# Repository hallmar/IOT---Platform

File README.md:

# Modular IOT Platform
Commissioned a modular IOT Platform for teaching purposes. There's a basic program in the 'Software' folder which is simply an IO test for the buttons and a test for the OLED.

Mouser Cart: https://www.mouser.com/ProjectManager/ProjectDetail.aspx?AccessID=9a8a02e45e

## Designed With

* Eagle CAD
* Arduino IDE

## Versioning
* 1.0 - [Hardware] Original hardware made
* 1.0 - [Software] Original 'basic' software written
## Authors

* **Hallmar Gauti Halldórsson**
* **Markus Pfeil**

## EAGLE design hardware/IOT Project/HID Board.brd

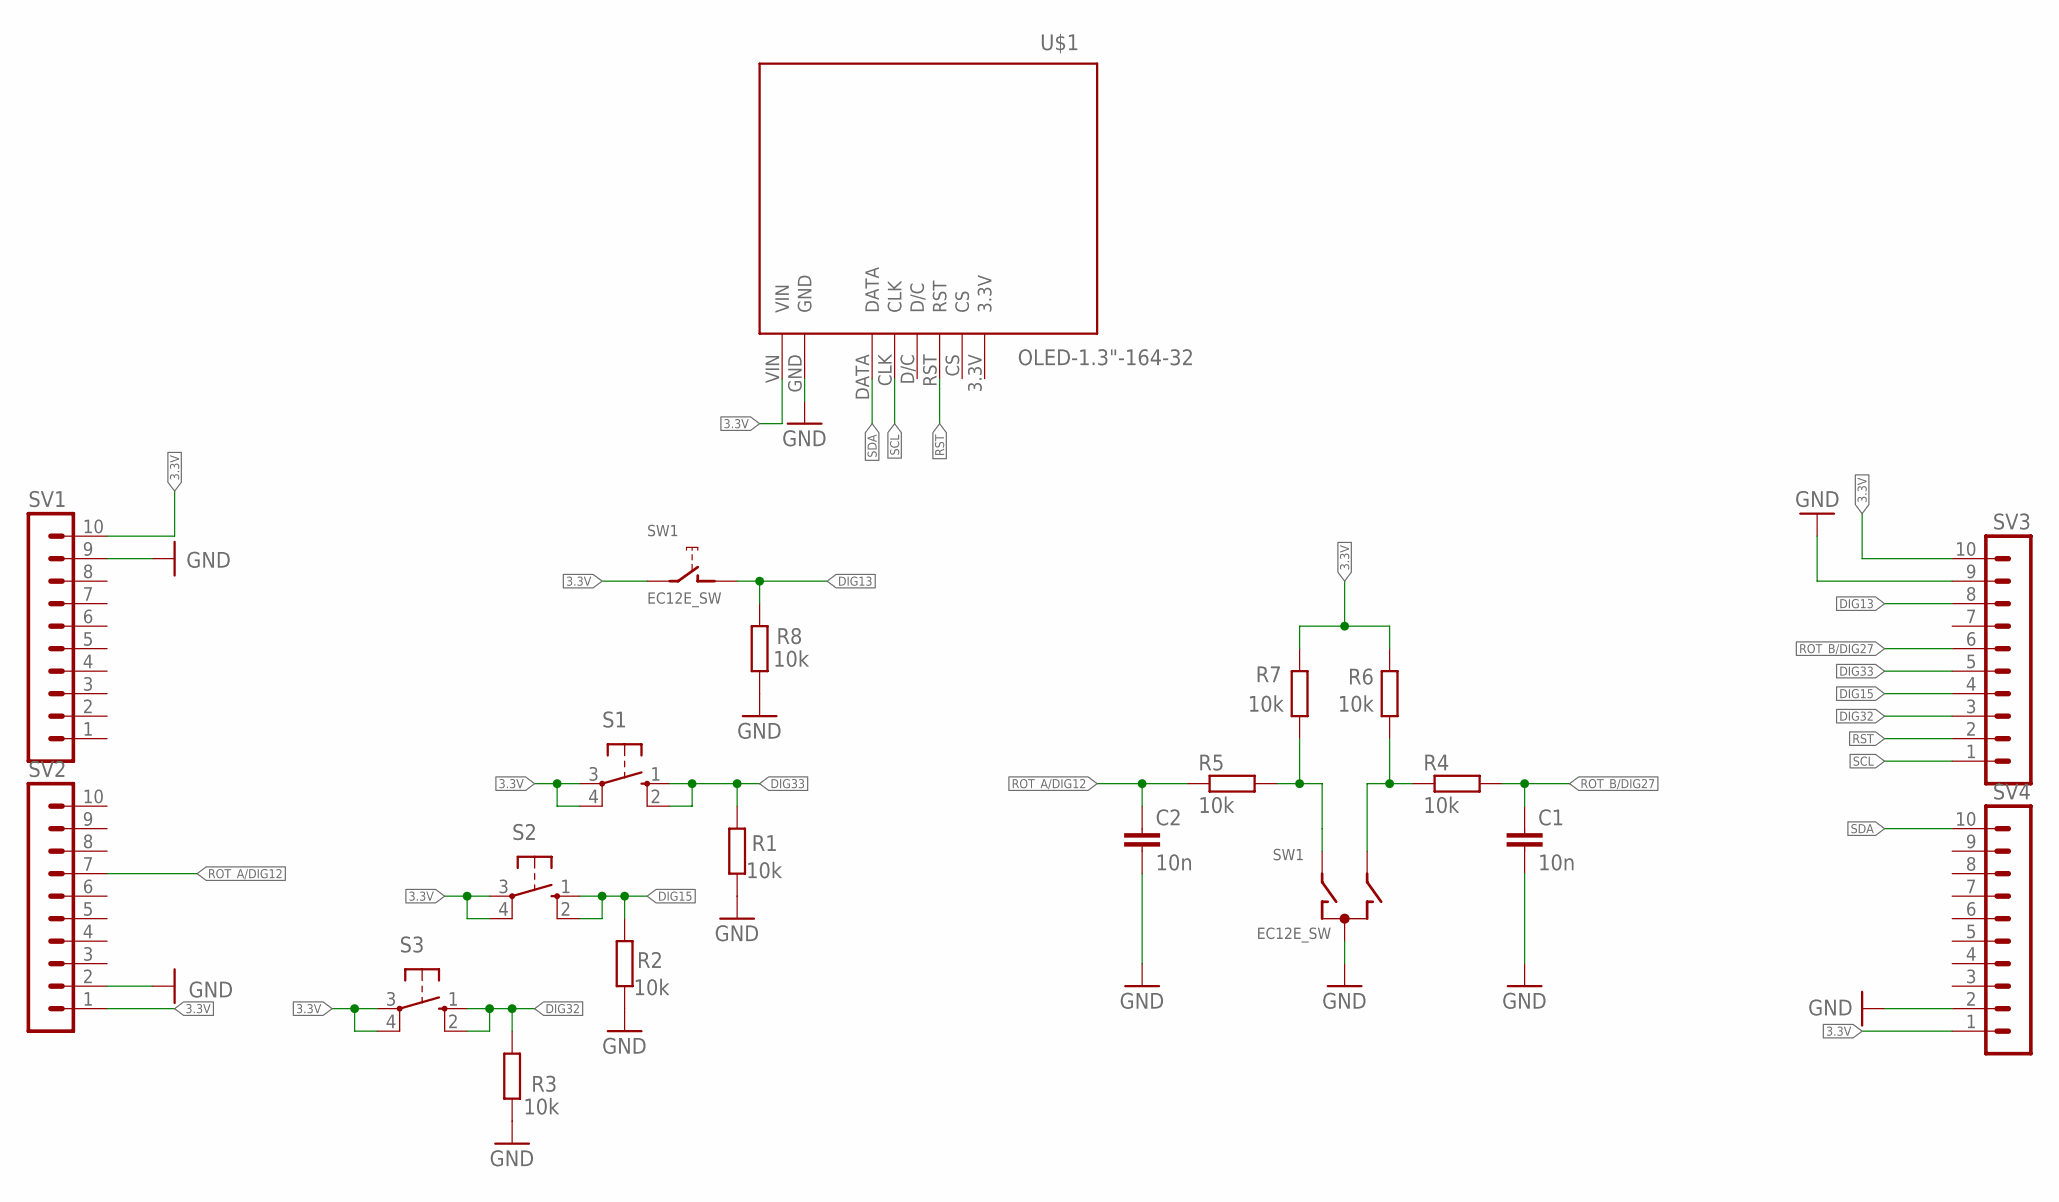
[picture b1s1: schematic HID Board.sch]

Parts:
C1, C2: 10n; C1206
R1, R2, R3, R4, R5, R6, R7, R8: 10k; M1206
S1, S2, S3: 10-XX; B3F-10XX
SV1, SV2, SV3, SV4: MA10-1
SW1: EC12E_SW; ALPS_EC12E_SW
U$1: OLED-1.3"-164-32

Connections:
3.3V: R6.2, R7.2, S1.3, S1.4 (P1), S2.3, S2.4 (P1), S3.3, S3.4 (P1), SV1.10, SV2.1, SV3.10, SV4.1, SW1.E (2), U$1.VIN
DIG13: R8.2, SV3.8, SW1.D (1)
DIG15: R2.2, S2.1 (S), S2.2 (S1), SV3.4
DIG32: R3.2, S3.1 (S), S3.2 (S1), SV3.3
DIG33: R1.2, S1.1 (S), S1.2 (S1), SV3.5
GND: C1.2, C2.2, R1.1, R2.1, R3.1, R8.1, SV1.9, SV2.2, SV3.9, SV4.2, SW1.C, U$1.GND
unnamed: R5.2, R7.1, SW1.A
unnamed: R4.1, R6.1, SW1.B
ROT_A/DIG12: C2.1, R5.1, SV2.7
ROT_B/DIG27: C1.1, R4.2, SV3.6
RST: SV3.2, U$1.RST
SCL: SV3.1, U$1.CLK
SDA: SV4.10, U$1.DATA

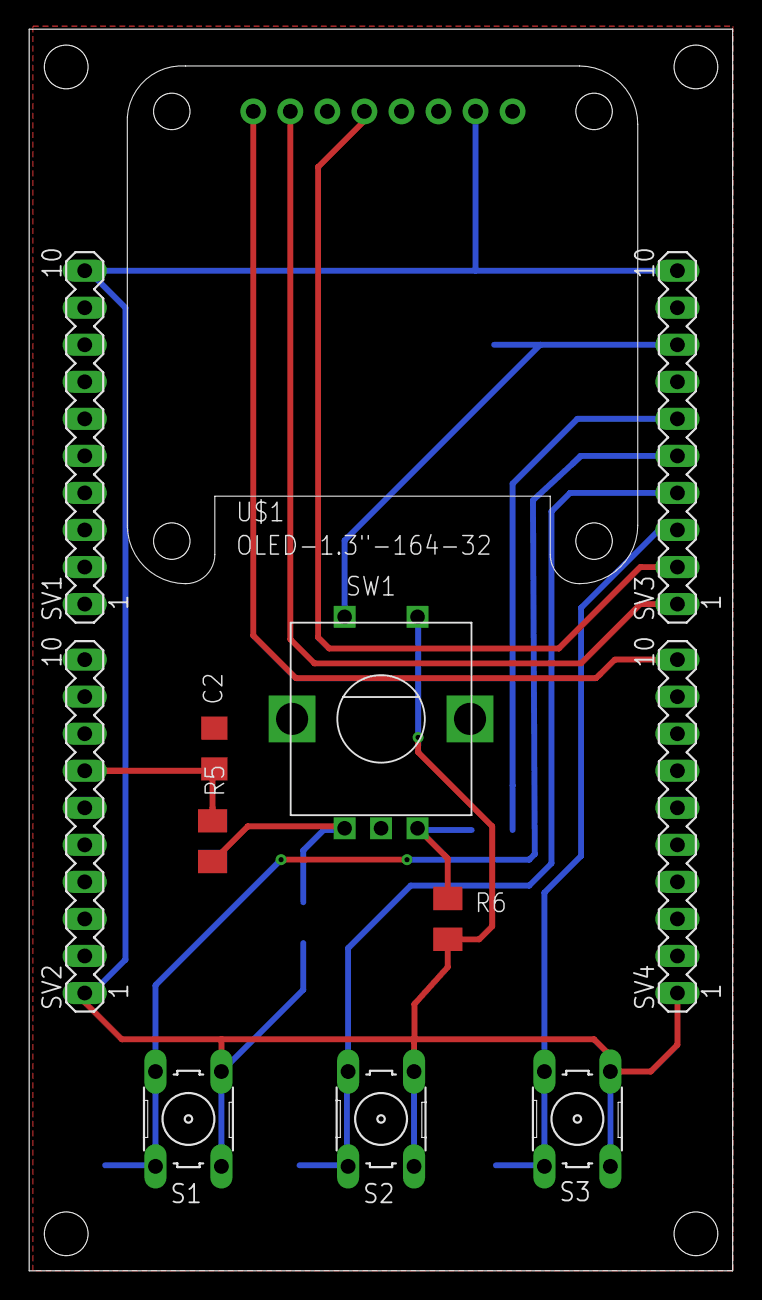
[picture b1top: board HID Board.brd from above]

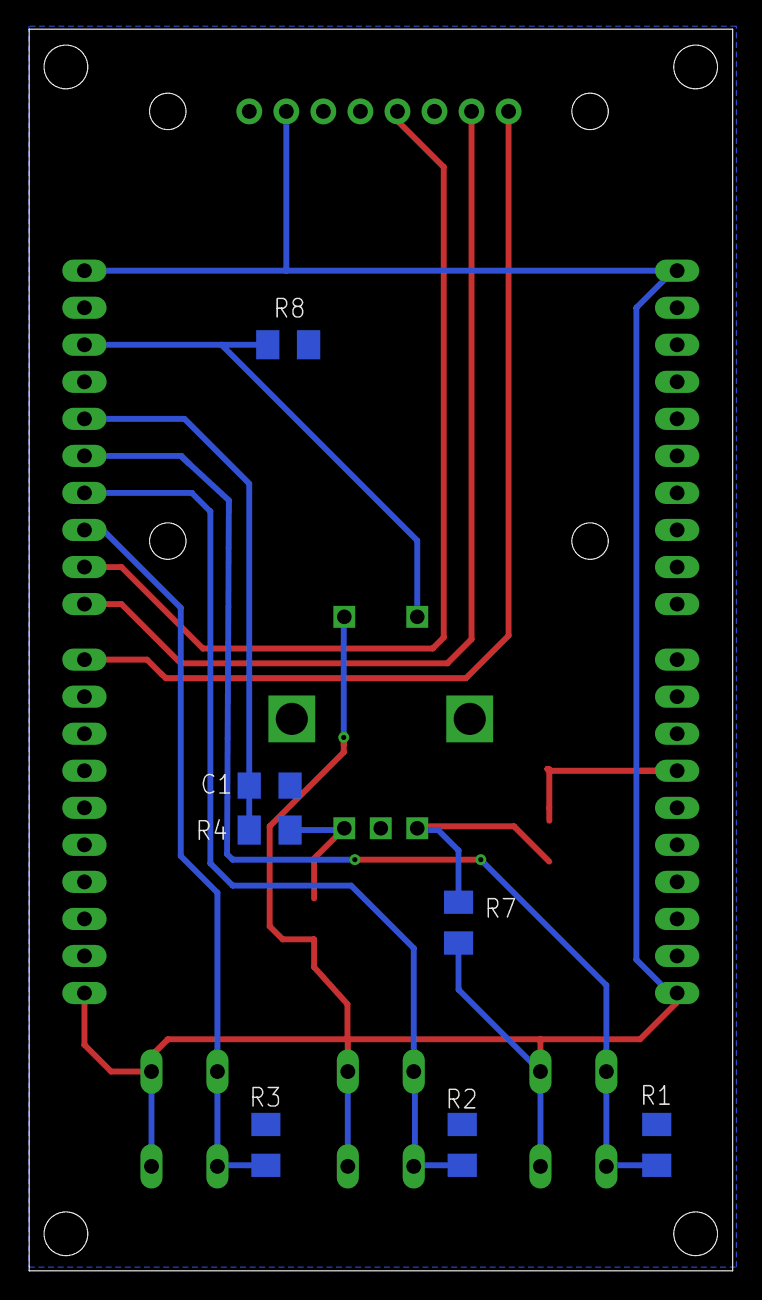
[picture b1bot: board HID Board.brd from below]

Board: 2 copper layers, 48.2 x 85.1 mm, 19 parts (7 on the bottom side), 13 nets.

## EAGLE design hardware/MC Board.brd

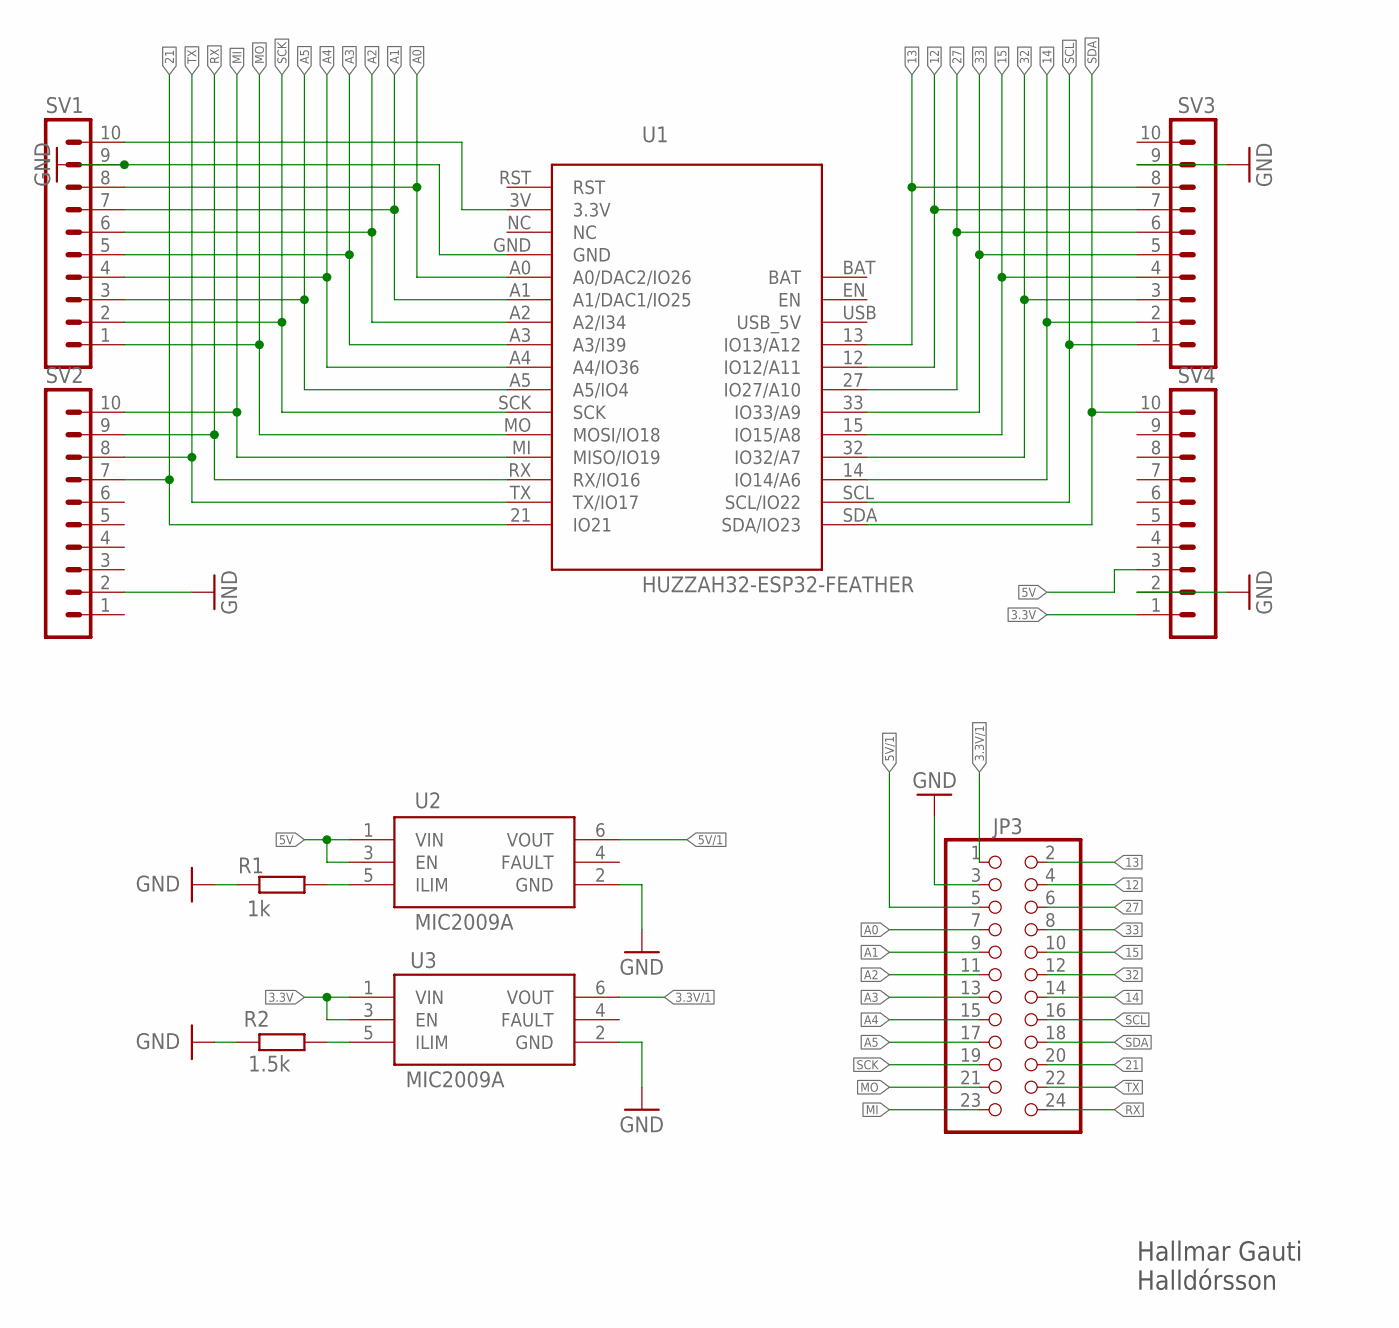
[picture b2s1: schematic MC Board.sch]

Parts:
JP3: PINHD-2X12/90; 2X12/90
R1: 1k; M1206
R2: 1.5k; M1206
SV1, SV2, SV3, SV4: MA10-1
U1: HUZZAH32-ESP32-FEATHER; ESP32-FEATHER
U2, U3: MIC2009A

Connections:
3.3V: SV4.1, U3.1 (VIN), U3.3 (EN)
3.3V/1: JP3.1, U3.6 (VOUT)
5V: SV4.3, U2.1 (VIN), U2.3 (EN)
5V/1: JP3.5, U2.6 (VOUT)
12: JP3.4, SV3.7, U1.12 (IO12/A11)
13: JP3.2, SV3.8, U1.13 (IO13/A12)
14: JP3.14, SV3.2, U1.14 (IO14/A6)
15: JP3.10, SV3.4, U1.15 (IO15/A8)
21: JP3.20, SV2.7, U1.21 (IO21)
27: JP3.6, SV3.6, U1.27 (IO27/A10)
32: JP3.12, SV3.3, U1.32 (IO32/A7)
33: JP3.8, SV3.5, U1.33 (IO33/A9)
A0: JP3.7, SV1.8, U1.A0 (A0/DAC2/IO26)
A1: JP3.9, SV1.7, U1.A1 (A1/DAC1/IO25)
A2: JP3.11, SV1.6, U1.A2 (A2/I34)
A3: JP3.13, SV1.5, U1.A3 (A3/I39)
A4: JP3.15, SV1.4, U1.A4 (A4/IO36)
A5: JP3.17, SV1.3, U1.A5 (A5/IO4)
GND: JP3.3, R1.2, R2.1, SV1.9, SV2.2, SV3.9, SV4.2, U1.GND, U2.2 (GND), U3.2 (GND)
MI: JP3.23, SV2.10, U1.MI (MISO/IO19)
MO: JP3.21, SV1.1, U1.MO (MOSI/IO18)
unnamed: SV1.10, U1.3V (3.3V)
unnamed: R2.2, U3.5 (ILIM)
unnamed: R1.1, U2.5 (ILIM)
RX: JP3.24, SV2.9, U1.RX (RX/IO16)
SCK: JP3.19, SV1.2, U1.SCK
SCL: JP3.16, SV3.1, U1.SCL (SCL/IO22)
SDA: JP3.18, SV4.10, U1.SDA (SDA/IO23)
TX: JP3.22, SV2.8, U1.TX (TX/IO17)

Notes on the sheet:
Hallmar Gauti Halldórsson

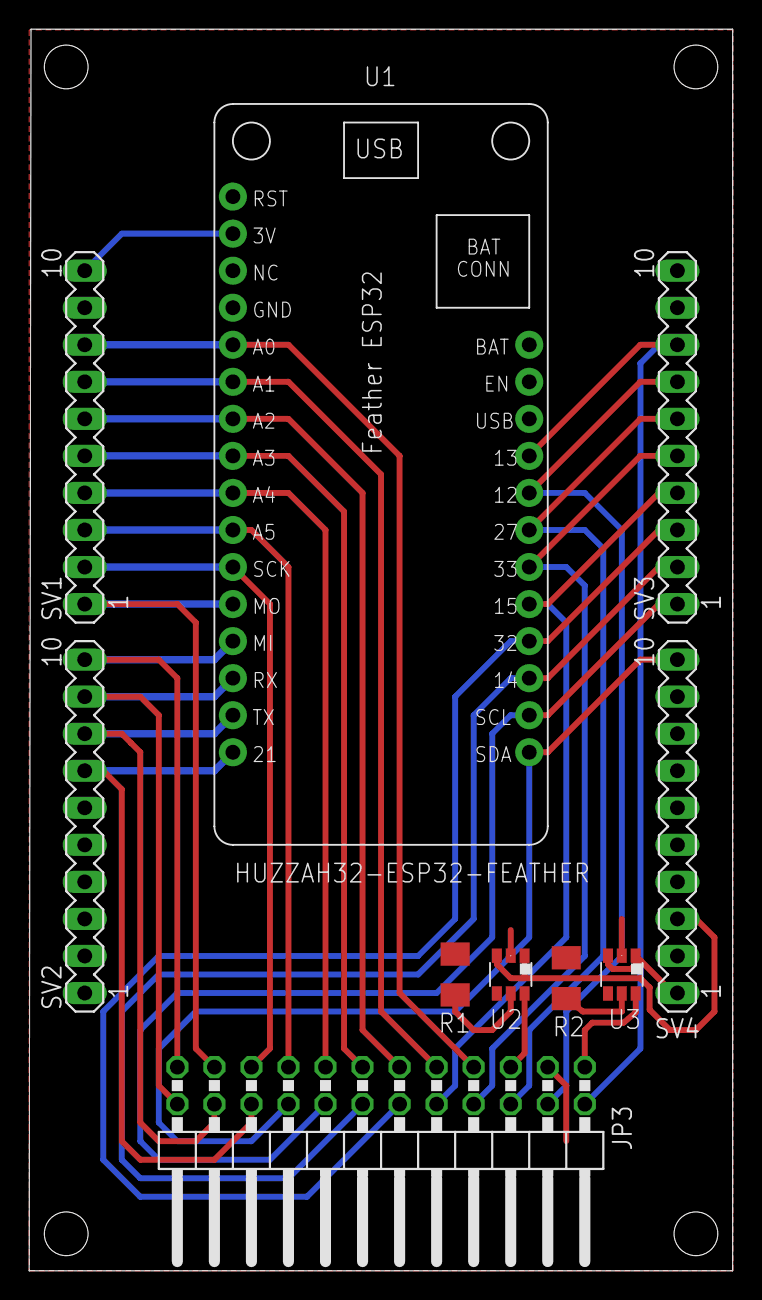
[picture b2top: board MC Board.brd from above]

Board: 2 copper layers, 48.2 x 85.1 mm, 10 parts (0 on the bottom side), 29 nets.

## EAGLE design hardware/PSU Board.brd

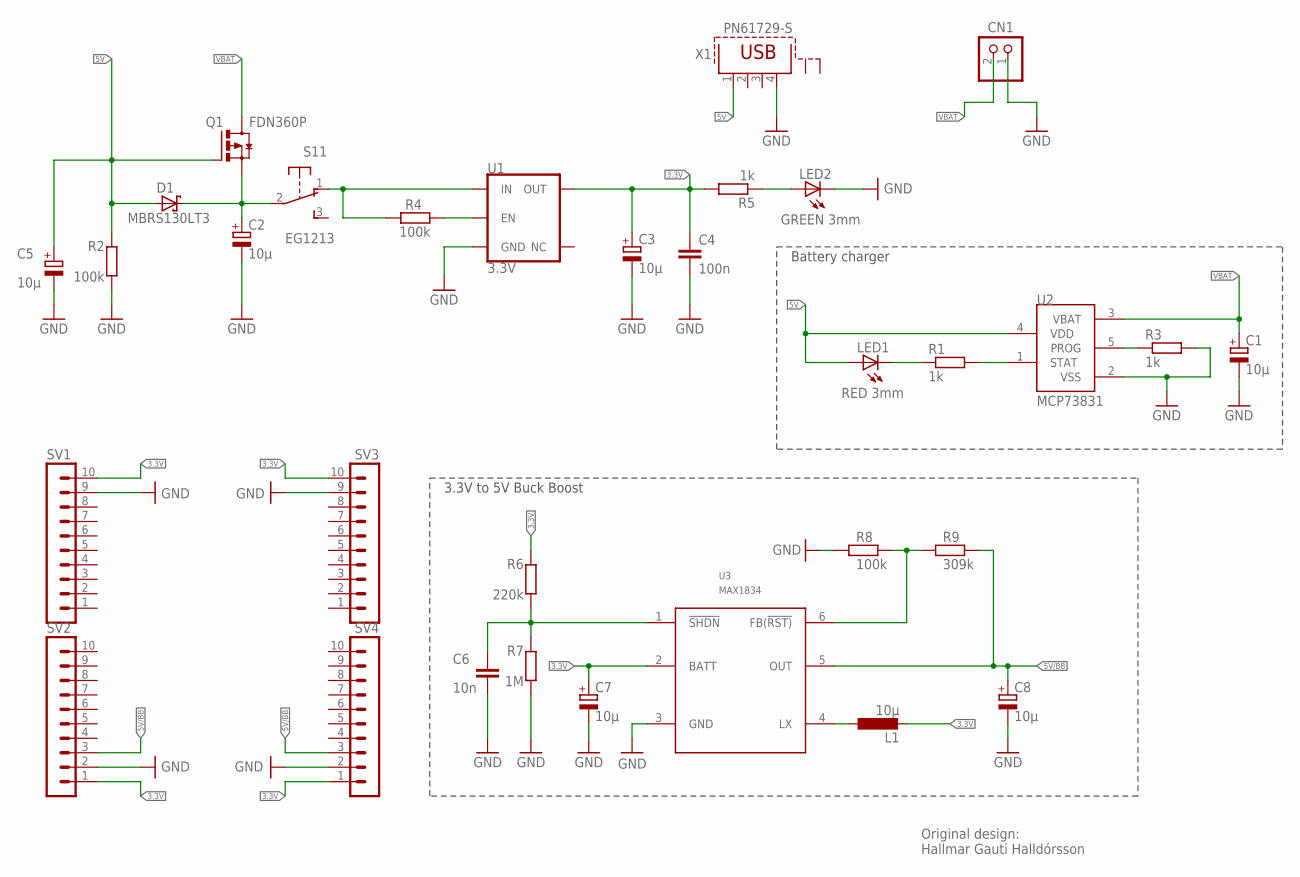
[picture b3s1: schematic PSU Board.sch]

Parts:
C1, C2, C3, C5, C7, C8: 10µ; 140CLH-0810
C4: 100n; C1206
C6: 10n; C1206
CN1: JST_2PIN-SMT; JST-PH-2-SMT
D1: MBRS130LT3; SMB
L1: 10µ; L3216C
LED1: RED 3mm; LED3MM
LED2: GREEN 3mm; LED3MM
Q1: FDN360P; SUPER-SOT3
R1, R3, R5: 1k; M1206
R2, R4, R8: 100k; M1206
R6: 220k; M1206
R7: 1M; M1206
R9: 309k; M1206
S1: EG1213
SV1, SV2, SV3, SV4: MA10-1
U1: 3.3V; SOT23-5
U2: MCP73831; SOT23-5L
U3: MAX1834; SOT23-6
X1: PN61729-S

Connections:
3.3V: C3.+, C4.1, C7.+, L1.2, R5.2, R6.2, SV1.10, SV2.1, SV3.10, SV4.1, U1.5 (OUT), U3.2 (BATT)
5V: C5.+, D1.A, LED1.A, Q1.1 (G), R2.2, U2.4 (VDD), X1.1
5V/BB: C8.+, R9.1, SV2.3, SV4.3, U3.5 (OUT)
GND: C1.-, C2.-, C3.-, C4.2, C5.-, C6.2, C7.-, C8.-, CN1.1 (2), LED2.K (C), R2.1, R3.2, R7.1, R8.2, SV1.9, SV2.2, SV3.9, SV4.2, U1.2 (GND), U2.2 (VSS), U3.3 (GND), X1.4
unnamed: C2.+, D1.C, Q1.2 (S), S1.2
unnamed: R1.2, U2.1 (STAT)
unnamed: R4.2, S1.1 (O), U1.1 (IN)
unnamed: LED1.K (C), R1.1
unnamed: R3.1, U2.5 (PROG)
unnamed: R4.1, U1.3 (EN)
unnamed: LED2.A, R5.1
unnamed: C6.1, R6.1, R7.2, U3.1 (!SHDN)
unnamed: L1.1, U3.4 (LX)
unnamed: R8.1, R9.2, U3.6 (FB(!RST))
VBAT: C1.+, CN1.2 (1), Q1.3 (D), U2.3 (VBAT)

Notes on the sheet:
Original design: Hallmar Gauti Halldórsson
Battery charger
3.3V to 5V Buck Boost

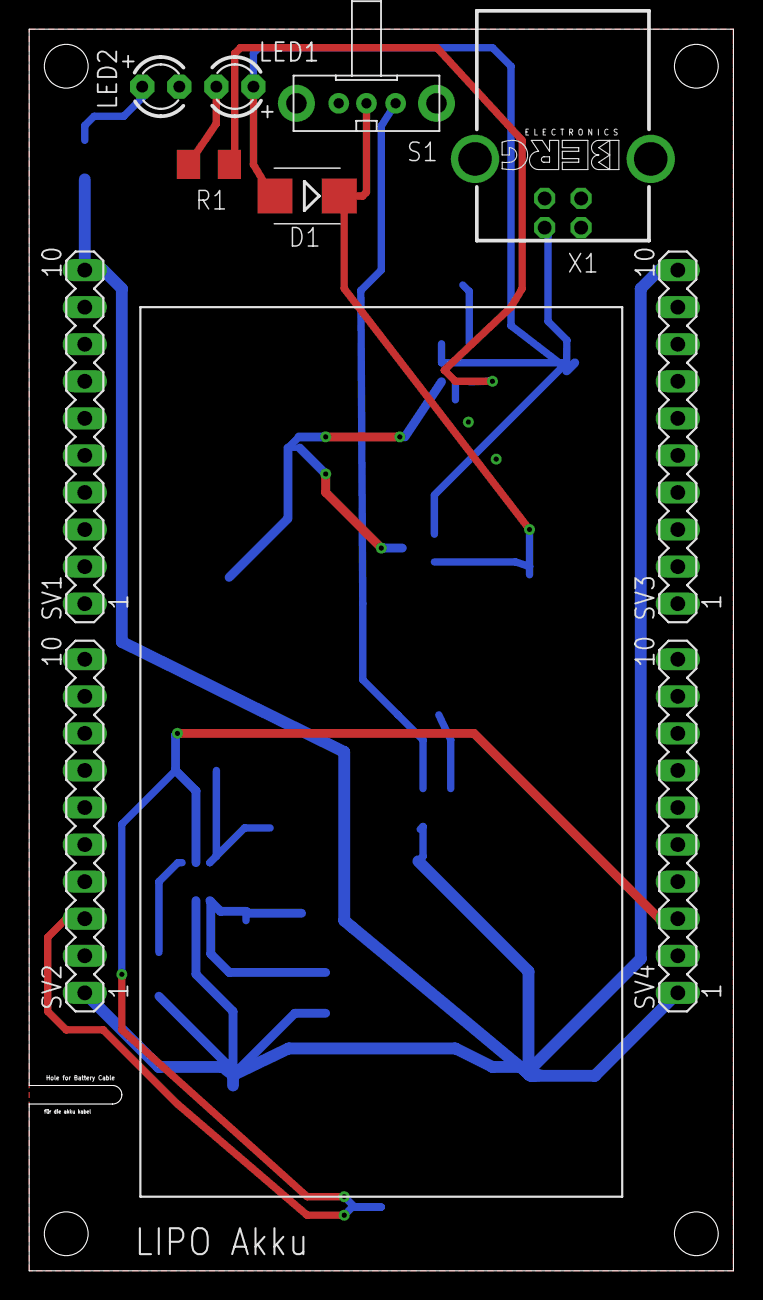
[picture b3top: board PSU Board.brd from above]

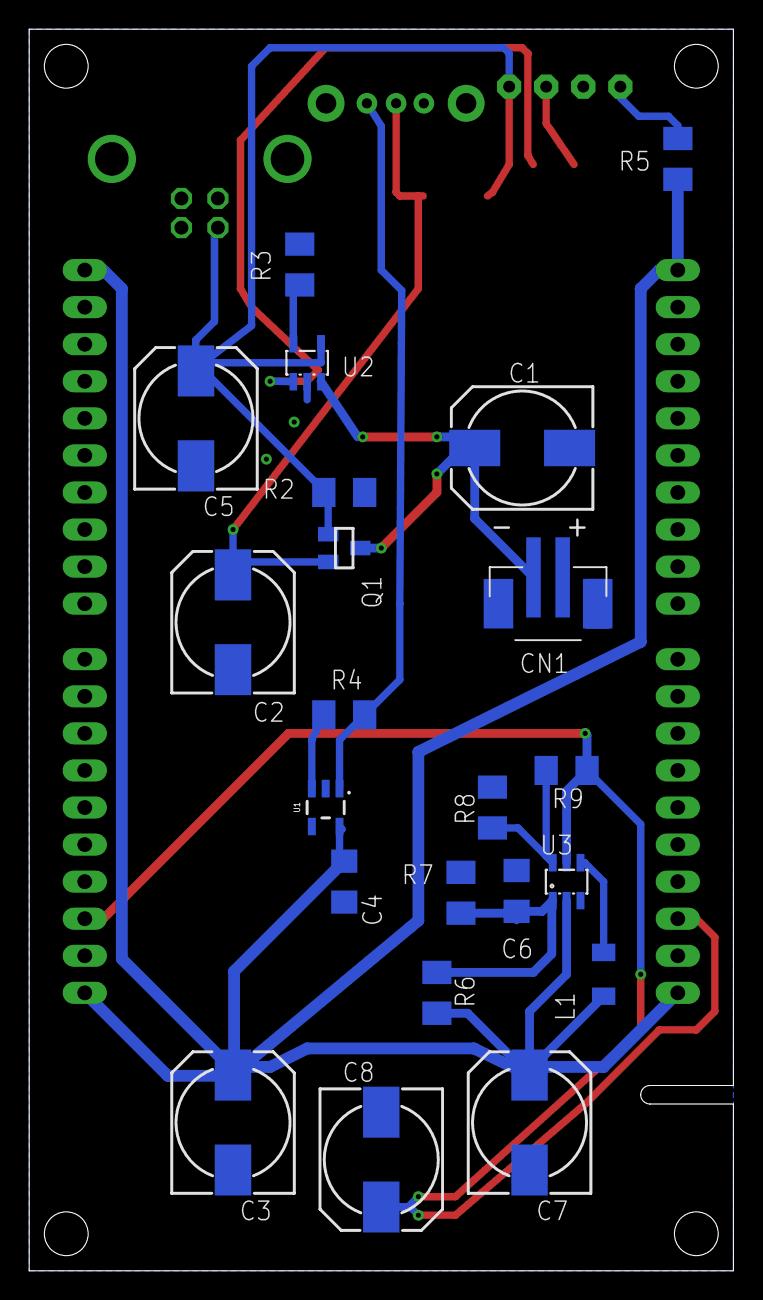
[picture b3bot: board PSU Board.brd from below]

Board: 2 copper layers, 48.3 x 85.1 mm, 32 parts (22 on the bottom side), 15 nets.

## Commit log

2020-09-20 images

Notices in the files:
parts and their libraries:
SparkFun-IC-Power: Licensing: Creative Commons ShareAlike 4.0 International - https://creativecommons.org/licenses/by-sa/4.0
